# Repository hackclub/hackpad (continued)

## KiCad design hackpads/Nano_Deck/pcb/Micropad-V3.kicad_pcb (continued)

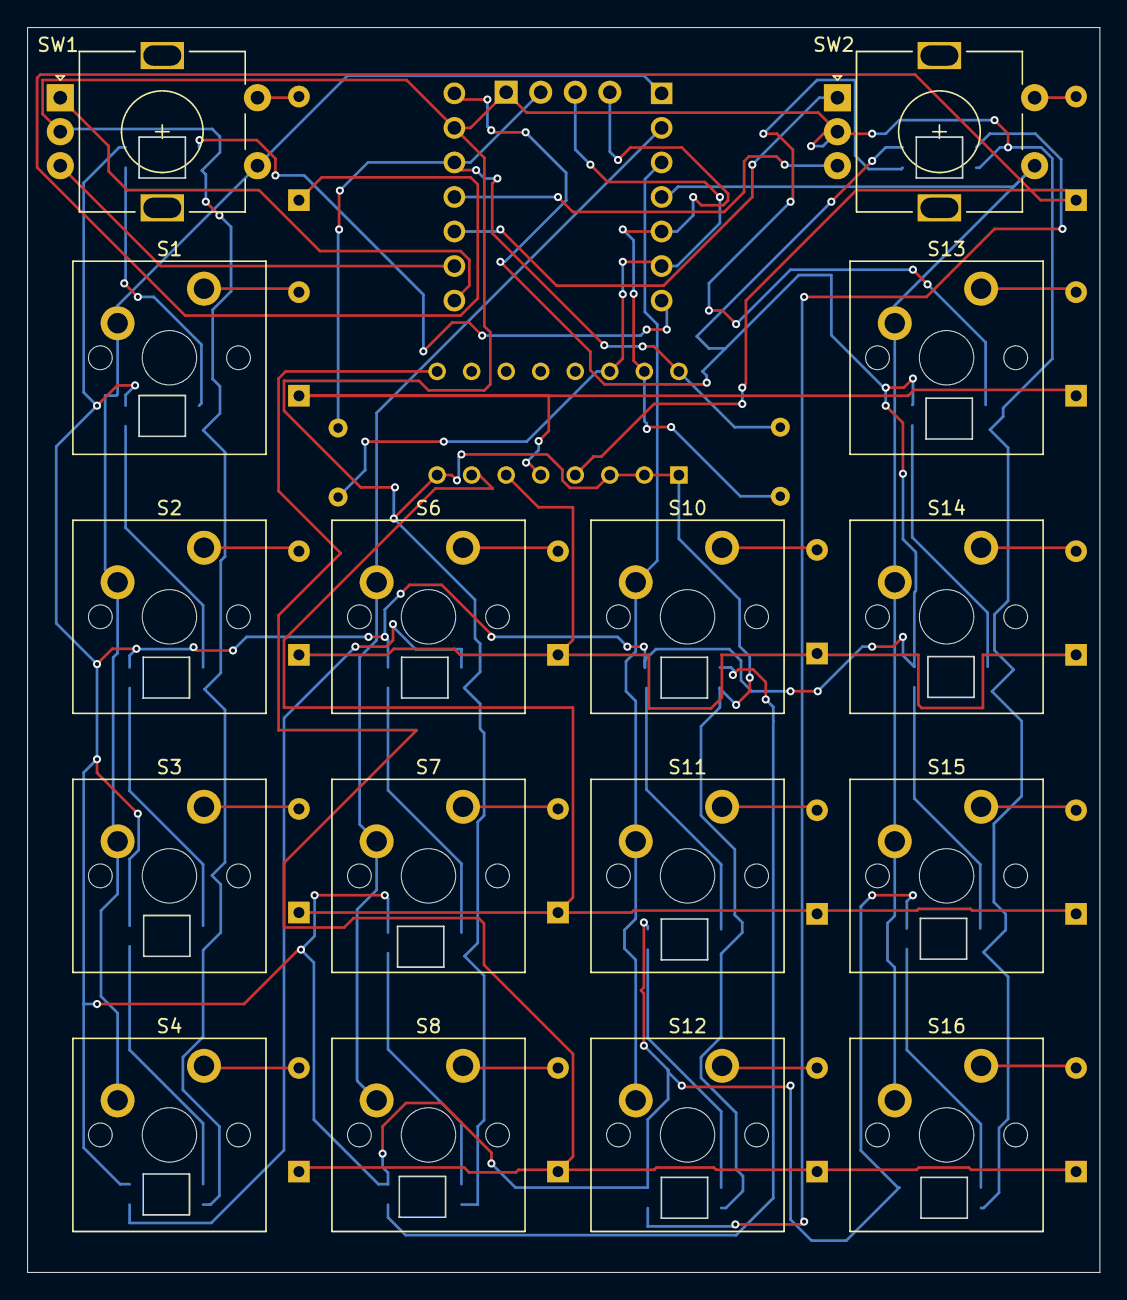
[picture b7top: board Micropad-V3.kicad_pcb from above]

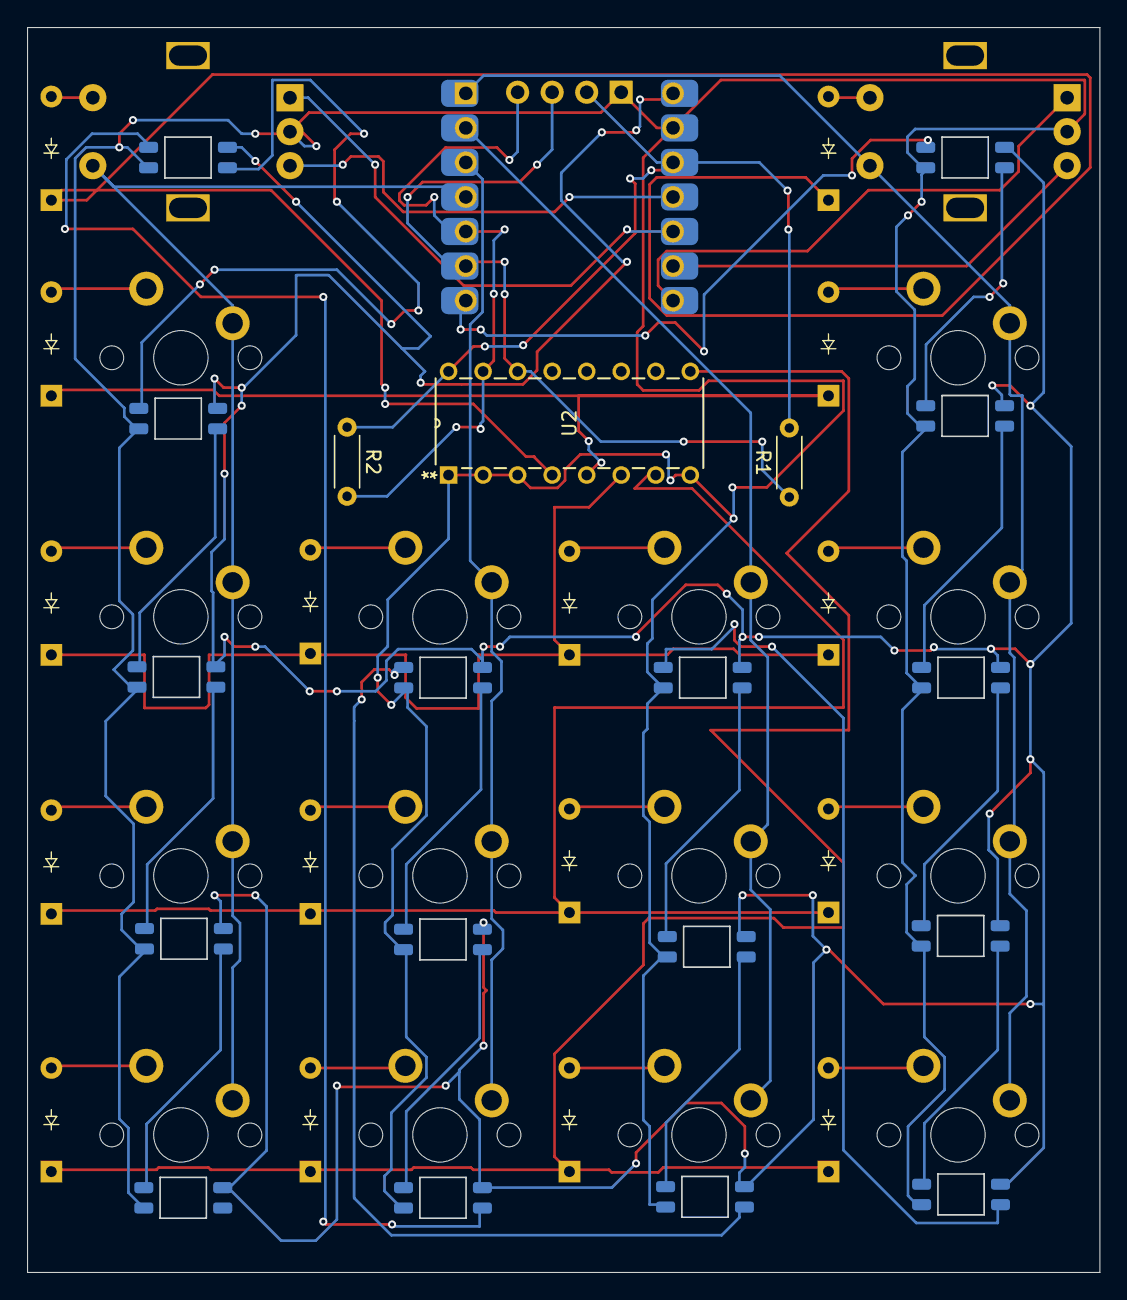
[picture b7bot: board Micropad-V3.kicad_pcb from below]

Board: 2 copper layers, 78.9 x 91.5 mm, 53 parts (36 on the bottom side), 50 nets.
